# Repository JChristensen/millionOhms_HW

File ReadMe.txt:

Million Ohms Project Hardware
Jack Christensen
V1.2 31Jul2012

This repository contains the following for the Million Ohms project:

Assembly Instructions
Schematic
Eagle Files

This work is licensed under the Creative Commons Attribution-ShareAlike 3.0
Unported License. To view a copy of this license, visit
http://creativecommons.org/licenses/by-sa/3.0/ or send a letter to Creative
Commons, 171 Second Street, Suite 300, San Francisco, California, 94105, USA.

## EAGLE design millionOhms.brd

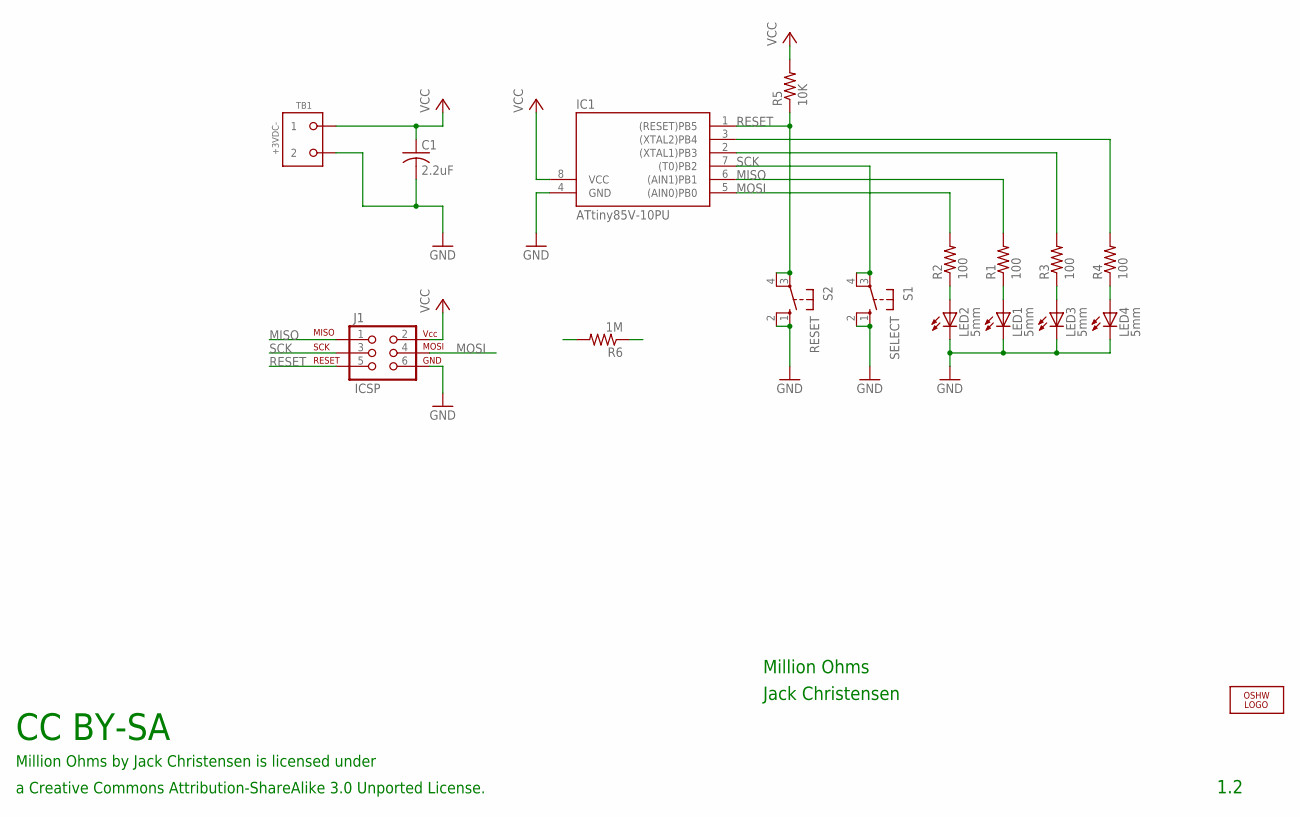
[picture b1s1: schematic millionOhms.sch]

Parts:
C1: 2.2uF; C025-025X050
IC1: ATtiny85V-10PU; DIL08
J1: ICSP; 2X3
LED1, LED2, LED3, LED4: 5mm; LED5MM
LOGO2: OSHW_LOGO_8MILX0150-NT; OSHW_8X150_NOTEXT
R1, R2, R3, R4: 100; 0204/6
R5: 10K; 0204/6
R6: 1M; 5616/20
S1: SELECT; B3F-10XXOCT
S2: RESET; B3F-10XXOCT
TB1: +3VDC-; OST-TB-2-3.5MM

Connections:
GND: C1.2, IC1.4 (GND), J1.6, LED1.K (C), LED2.K (C), LED3.K (C), LED4.K (C), S1.1 (S), S1.2 (S1), S2.1 (S), S2.2 (S1), TB1.P$2 (2)
MISO: IC1.6 ((AIN1)PB1), J1.1, R1.2
MOSI: IC1.5 ((AIN0)PB0), J1.4, R2.2
unnamed: LED2.A, R2.1
unnamed: LED1.A, R1.1
unnamed: LED3.A, R3.1
unnamed: LED4.A, R4.1
unnamed: IC1.2 ((XTAL1)PB3), R3.2
unnamed: IC1.3 ((XTAL2)PB4), R4.2
RESET: IC1.1 ((RESET)PB5), J1.5, R5.1, S2.3, S2.4 (P1)
SCK: IC1.7 ((T0)PB2), J1.3, S1.3, S1.4 (P1)
VCC: C1.1, IC1.8 (VCC), J1.2, R5.2, TB1.P$1 (1)

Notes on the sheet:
Million Ohms by Jack Christensen is licensed under
CC BY-SA
a Creative Commons Attribution-ShareAlike 3.0 Unported License.
Million Ohms
Jack Christensen
1.2

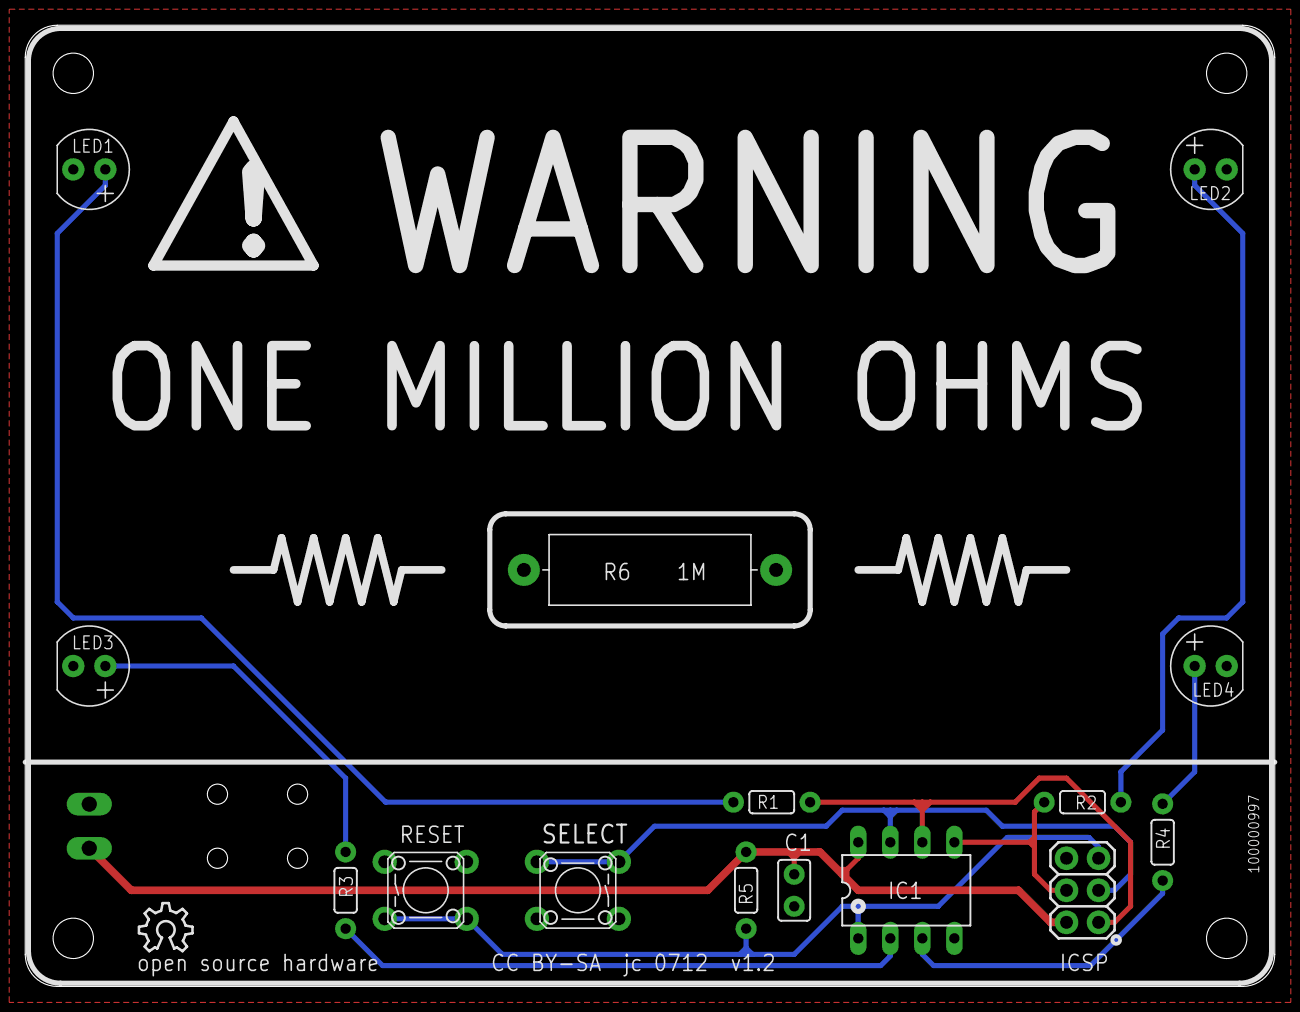
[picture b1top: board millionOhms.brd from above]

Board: 2 copper layers, 99.1 x 76.2 mm, 17 parts (1 on the bottom side), 12 nets.

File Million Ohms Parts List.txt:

"Million Ohms" Project Partslist
Jack Christensen
V1.1 Oct-2011

A bill of materials is available at:
http://www.mouser.com:80/ProjectManager/ProjectDetail.aspx?A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

C1		100nF ceramic
C2		10uF electrolytic
IC1		Atmel microcontroller, ATtiny45V-10PU or ATtiny85V-10PU
J1		ICSP header, 0.1" pitch, 2x3 (Optional)
LED1-4	5mm LED
R1-4	100 ohm, 1/8W or 1/6W
R5		10K, 1/8W or 1/6W
R6		1M, 2W
SELECT	6mm tactile button switch
RESET	6mm tactile button switch (Optional)
TB1		Terminal block, 3.5mm pitch, two position
		Battery holder, 2xAA
		3M double-stick foam tape
		
Assembly tips

1. Observe polarity when installing the LEDs, microcontroller, electrolytic capacitor, and when connecting the batteries to the terminal block (red wire is +, black is -).

2. Location of the terminal block and battery holder is flexible depending on your intended use and installation of the board.  I put the terminal block and the battery holder on the back side of the circuit board, using a one-inch square of double-stick foam tape to fasten the battery holder about 0.25 inch (6mm) from the bottom of the board.  This allows it to stand up at a slight angle on my desk.

3. There are four holes in the circuit board near the terminal block.  These can be used as strain reliefs for the battery wires by threading the wires through the holes.  Where you locate the battery holder, whether you use the strain relief holes, and how long you leave the wires from the battery holder all depend on your personal preference and installation.

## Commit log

2011-11-20 V1.1
2012-08-01 Hardware v1.2
